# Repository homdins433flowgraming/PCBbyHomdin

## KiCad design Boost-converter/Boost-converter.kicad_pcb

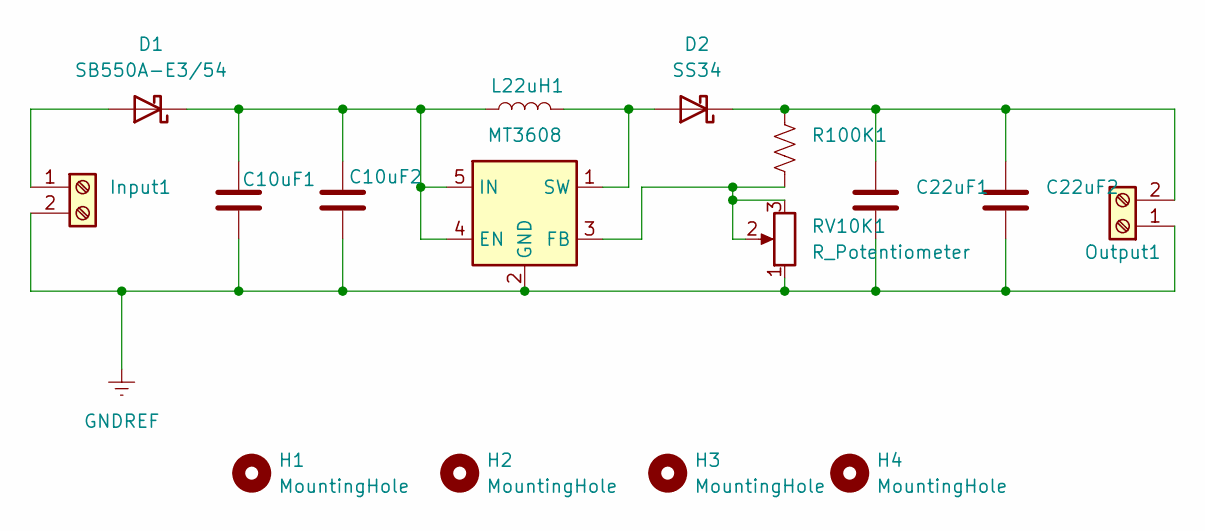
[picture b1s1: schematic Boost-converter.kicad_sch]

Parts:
C10uF1, C10uF2: C; C_0805_2012Metric_Pad1.18x1.45mm_HandSolder
C22uF1, C22uF2: C; C_1210_3225Metric_Pad1.33x2.70mm_HandSolder
D1: SB550A-E3/54; D_DO-201AD_P15.24mm_Horizontal
D2: SS34; D_SMA
H1, H2, H3, H4: MountingHole; MountingHole_3.2mm_M3_ISO14580_Pad
Input1: Screw_Terminal_01x02; TerminalBlock_Phoenix_MKDS-1,5-2_1x02_P5.00mm_Horizontal
L22uH1: L; L_12x12mm_H8mm
Output1: Screw_Terminal_01x02; TerminalBlock_Phoenix_MKDS-1,5-2_1x02_P5.00mm_Horizontal
R100K1: R_US; R_0805_2012Metric_Pad1.20x1.40mm_HandSolder
RV10K1: R_Potentiometer; Potentiometer_Bourns_3296W_Vertical
U1: MT3608; SOT-23-6

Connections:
GNDREF: C10uF1.2, C10uF2.2, C22uF1.2, C22uF2.2, Input1.2, Output1.1, RV10K1.1, U1.2 (GND)
unnamed: D1.2 (A), Input1.1
unnamed: C10uF1.1, C10uF2.1, D1.1 (K), L22uH1.1, U1.4 (EN), U1.5 (IN)
unnamed: D2.2 (A), L22uH1.2, U1.1 (SW)
unnamed: C22uF1.1, C22uF2.1, D2.1 (K), Output1.2, R100K1.1
unnamed: R100K1.2, RV10K1.2, RV10K1.3, U1.3 (FB)

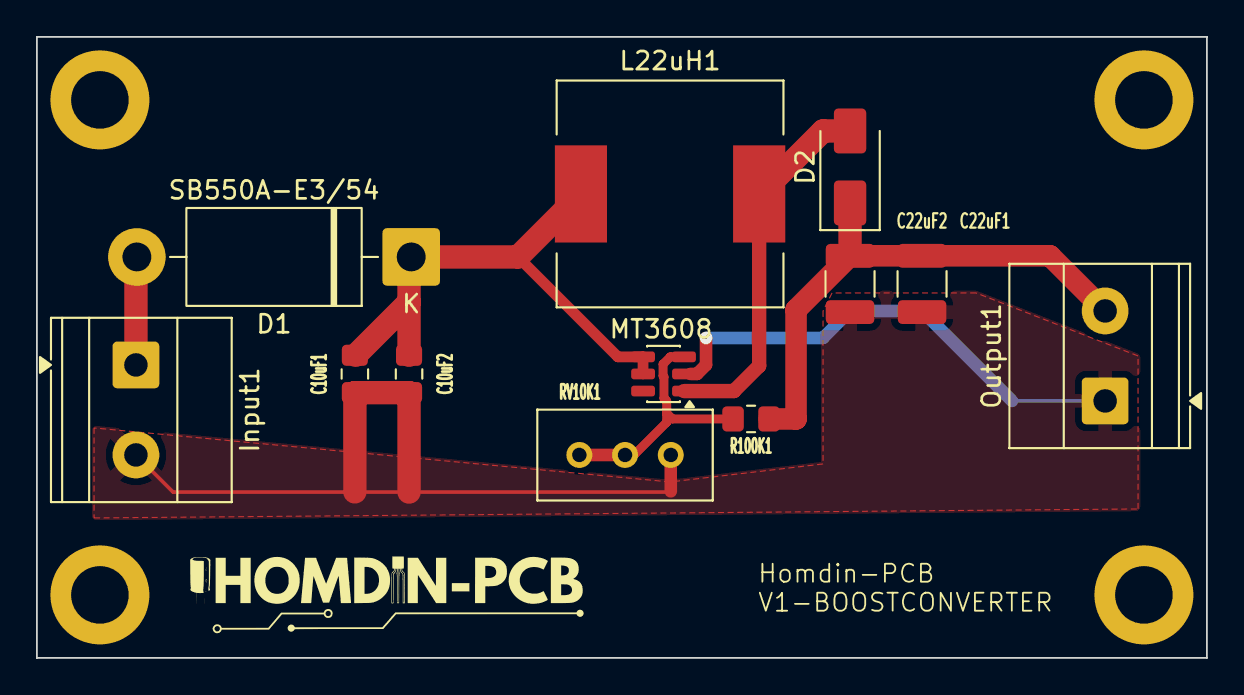
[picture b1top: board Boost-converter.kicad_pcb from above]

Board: 2 copper layers, 65.0 x 34.5 mm, 16 parts (0 on the bottom side), 6 nets.

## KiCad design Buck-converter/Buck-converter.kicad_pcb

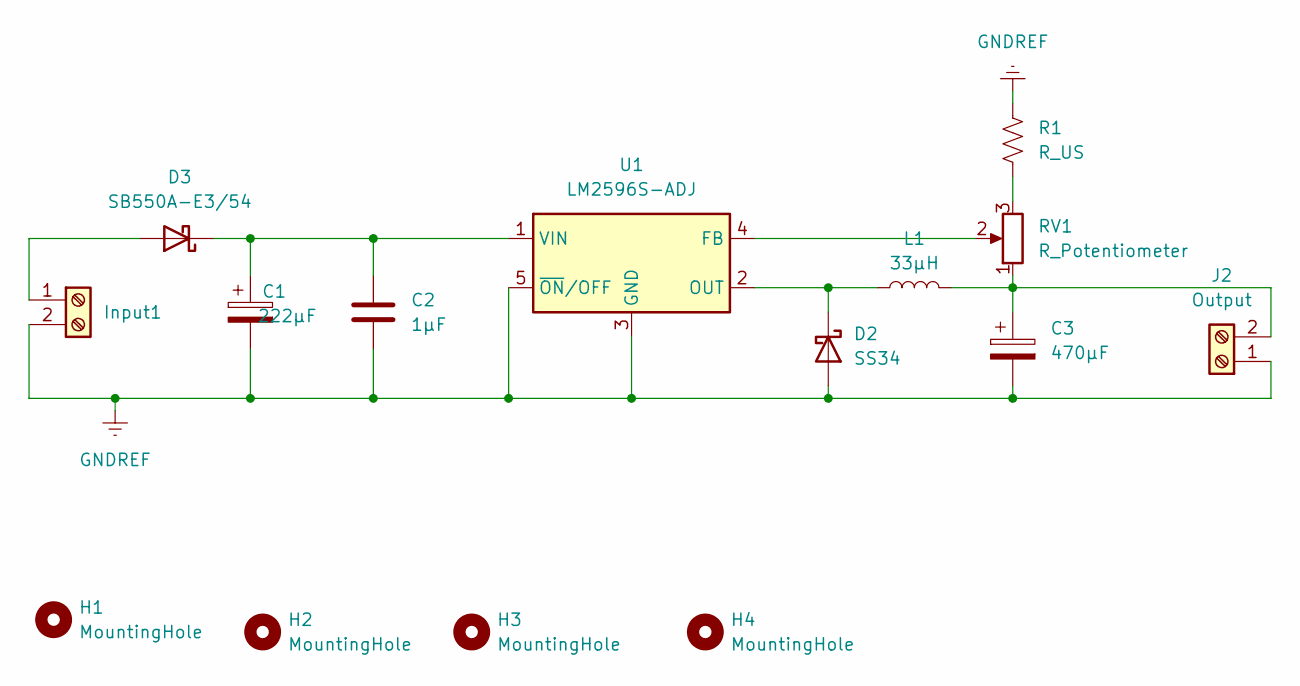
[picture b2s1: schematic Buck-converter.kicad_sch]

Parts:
C1: 222μF; C_Radial_D10.0mm_H12.5mm_P5.00mm
C2: 1μF; C_0603_1608Metric_Pad1.08x0.95mm_HandSolder
C3: 470μF; C_Radial_D10.0mm_H16.0mm_P5.00mm
D2: SS34; D_SMA
D3: SB550A-E3/54; D_DO-201AD_P15.24mm_Horizontal
H1, H2, H3, H4: MountingHole; MountingHole_3.2mm_M3_ISO14580_Pad
Input1: Screw_Terminal_01x02; TerminalBlock_Phoenix_MKDS-1,5-2_1x02_P5.00mm_Horizontal
J2: Output; TerminalBlock_Phoenix_MKDS-1,5-2_1x02_P5.00mm_Horizontal
L1: 33μH; L_Bourns_SRP1038C_10.0x10.0mm
R1: R_US; R_0805_2012Metric_Pad1.20x1.40mm_HandSolder
RV1: R_Potentiometer; Potentiometer_Bourns_3296W_Vertical
U1: LM2596S-ADJ; TO-263-5_TabPin3

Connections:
GNDREF: C1.2, C2.2, C3.2, D2.2 (A), Input1.2, J2.1, R1.1, U1.3 (GND), U1.5 (~ON/OFF)
unnamed: D2.1 (K), L1.1, U1.2 (OUT)
unnamed: D3.2 (A), Input1.1
unnamed: C1.1, C2.1, D3.1 (K), U1.1 (VIN)
unnamed: C3.1, J2.2, L1.2, RV1.1
unnamed: R1.2, RV1.3
unnamed: RV1.2, U1.4 (FB)

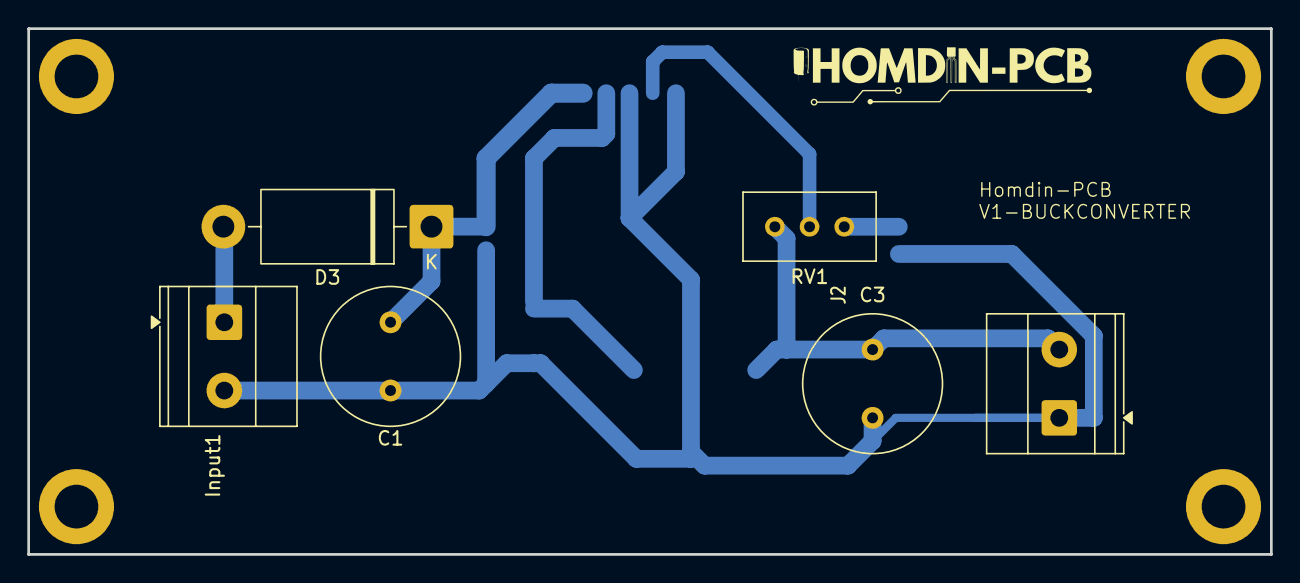
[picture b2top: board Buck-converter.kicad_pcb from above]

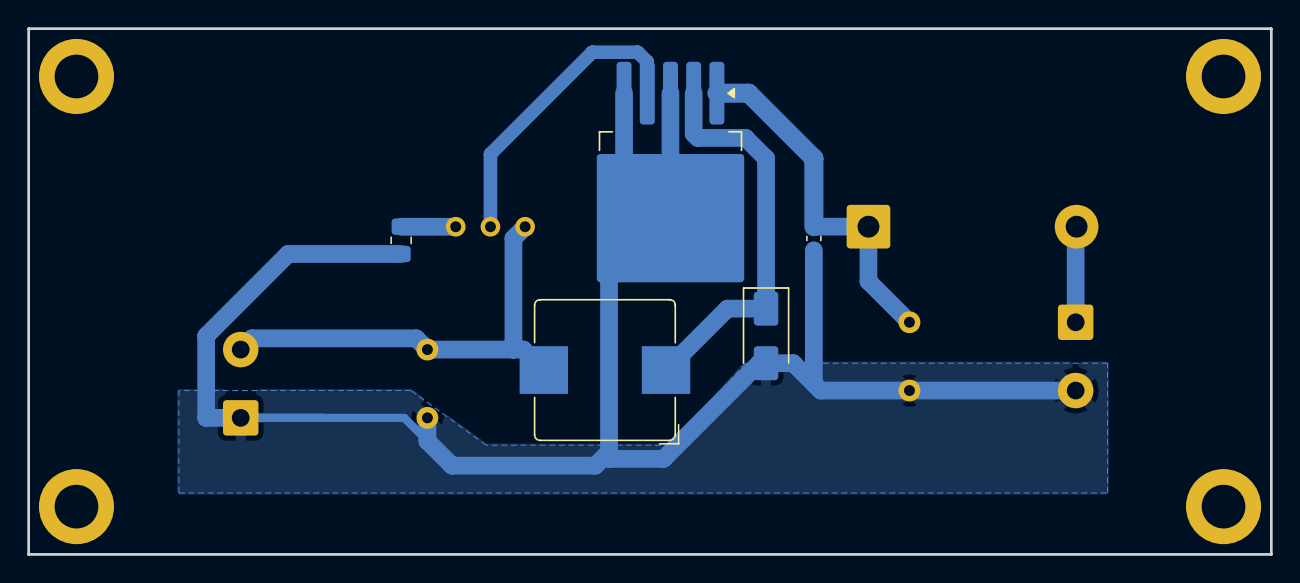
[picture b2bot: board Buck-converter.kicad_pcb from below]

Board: 2 copper layers, 91.0 x 38.5 mm, 15 parts (5 on the bottom side), 7 nets.
